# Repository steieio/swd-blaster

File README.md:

# Arm Cortex SWD Header to Altera Blaster Adapter

This design adapts the 10 pin 50 mil picth JTAG header pinout used by Arm to the 10 pin 100 mil pitch header pinout used by Altera for their Blasters.  It works great with the [Tigard board](https://www.crowdsupply.com/securinghw/tigard) and [openFPGALoader](https://github.com/trabucayre/openFPGALoader).

You can [order the PCB inexpensively from OSH Park](https://oshpark.com/shared_projects/WjwHzZBt).
I've included [a PDF version of the schematic](swd-blaster.pdf) for convenience.

Here is the board being used to connect Tigard to the MAX10 10M08 Evaluation Kit:

Here are some additional images of the board:

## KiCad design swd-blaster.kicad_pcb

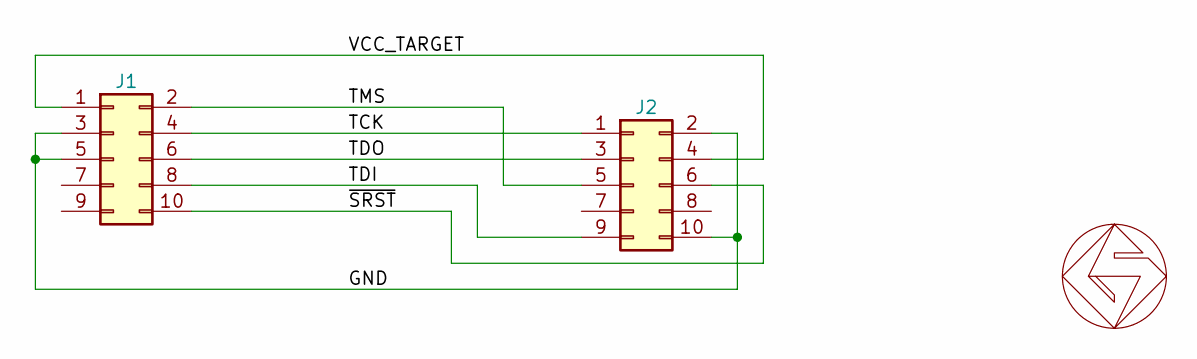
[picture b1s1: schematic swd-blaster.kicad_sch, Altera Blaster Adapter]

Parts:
GS1: GS_logo; gs_logo_200mil
J1: Conn_02x05_Counter_Clockwise; PinHeader_2x05_P1.27mm_Vertical_SMD; MPN 20021521-00010T1LF; LCSC C2972785
J2: Conn_02x05_Counter_Clockwise; PinSocket_2x05_P100mil_Board_Tab; MPN FH-00843; LCSC C2685127

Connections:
/GND: J1.3, J1.5, J2.2, J2.10
/TCK: J1.4, J2.1
/TDI: J1.8, J2.9
/TDO: J1.6, J2.3
/TMS: J1.2, J2.5
/VCC_TARGET: J1.1, J2.4
/~SRST: J1.10, J2.6

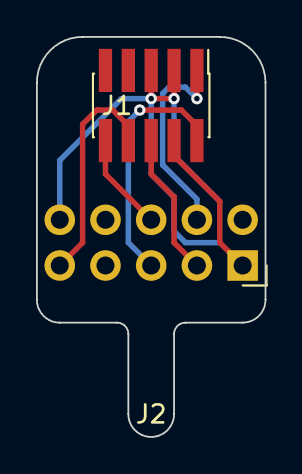
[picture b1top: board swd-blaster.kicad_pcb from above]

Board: 2 copper layers, 12.7 x 22.2 mm, 3 parts (1 on the bottom side), 7 nets.

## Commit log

2024-10-05 initial commit of completed design for sharing
2024-10-05 fixed image link
